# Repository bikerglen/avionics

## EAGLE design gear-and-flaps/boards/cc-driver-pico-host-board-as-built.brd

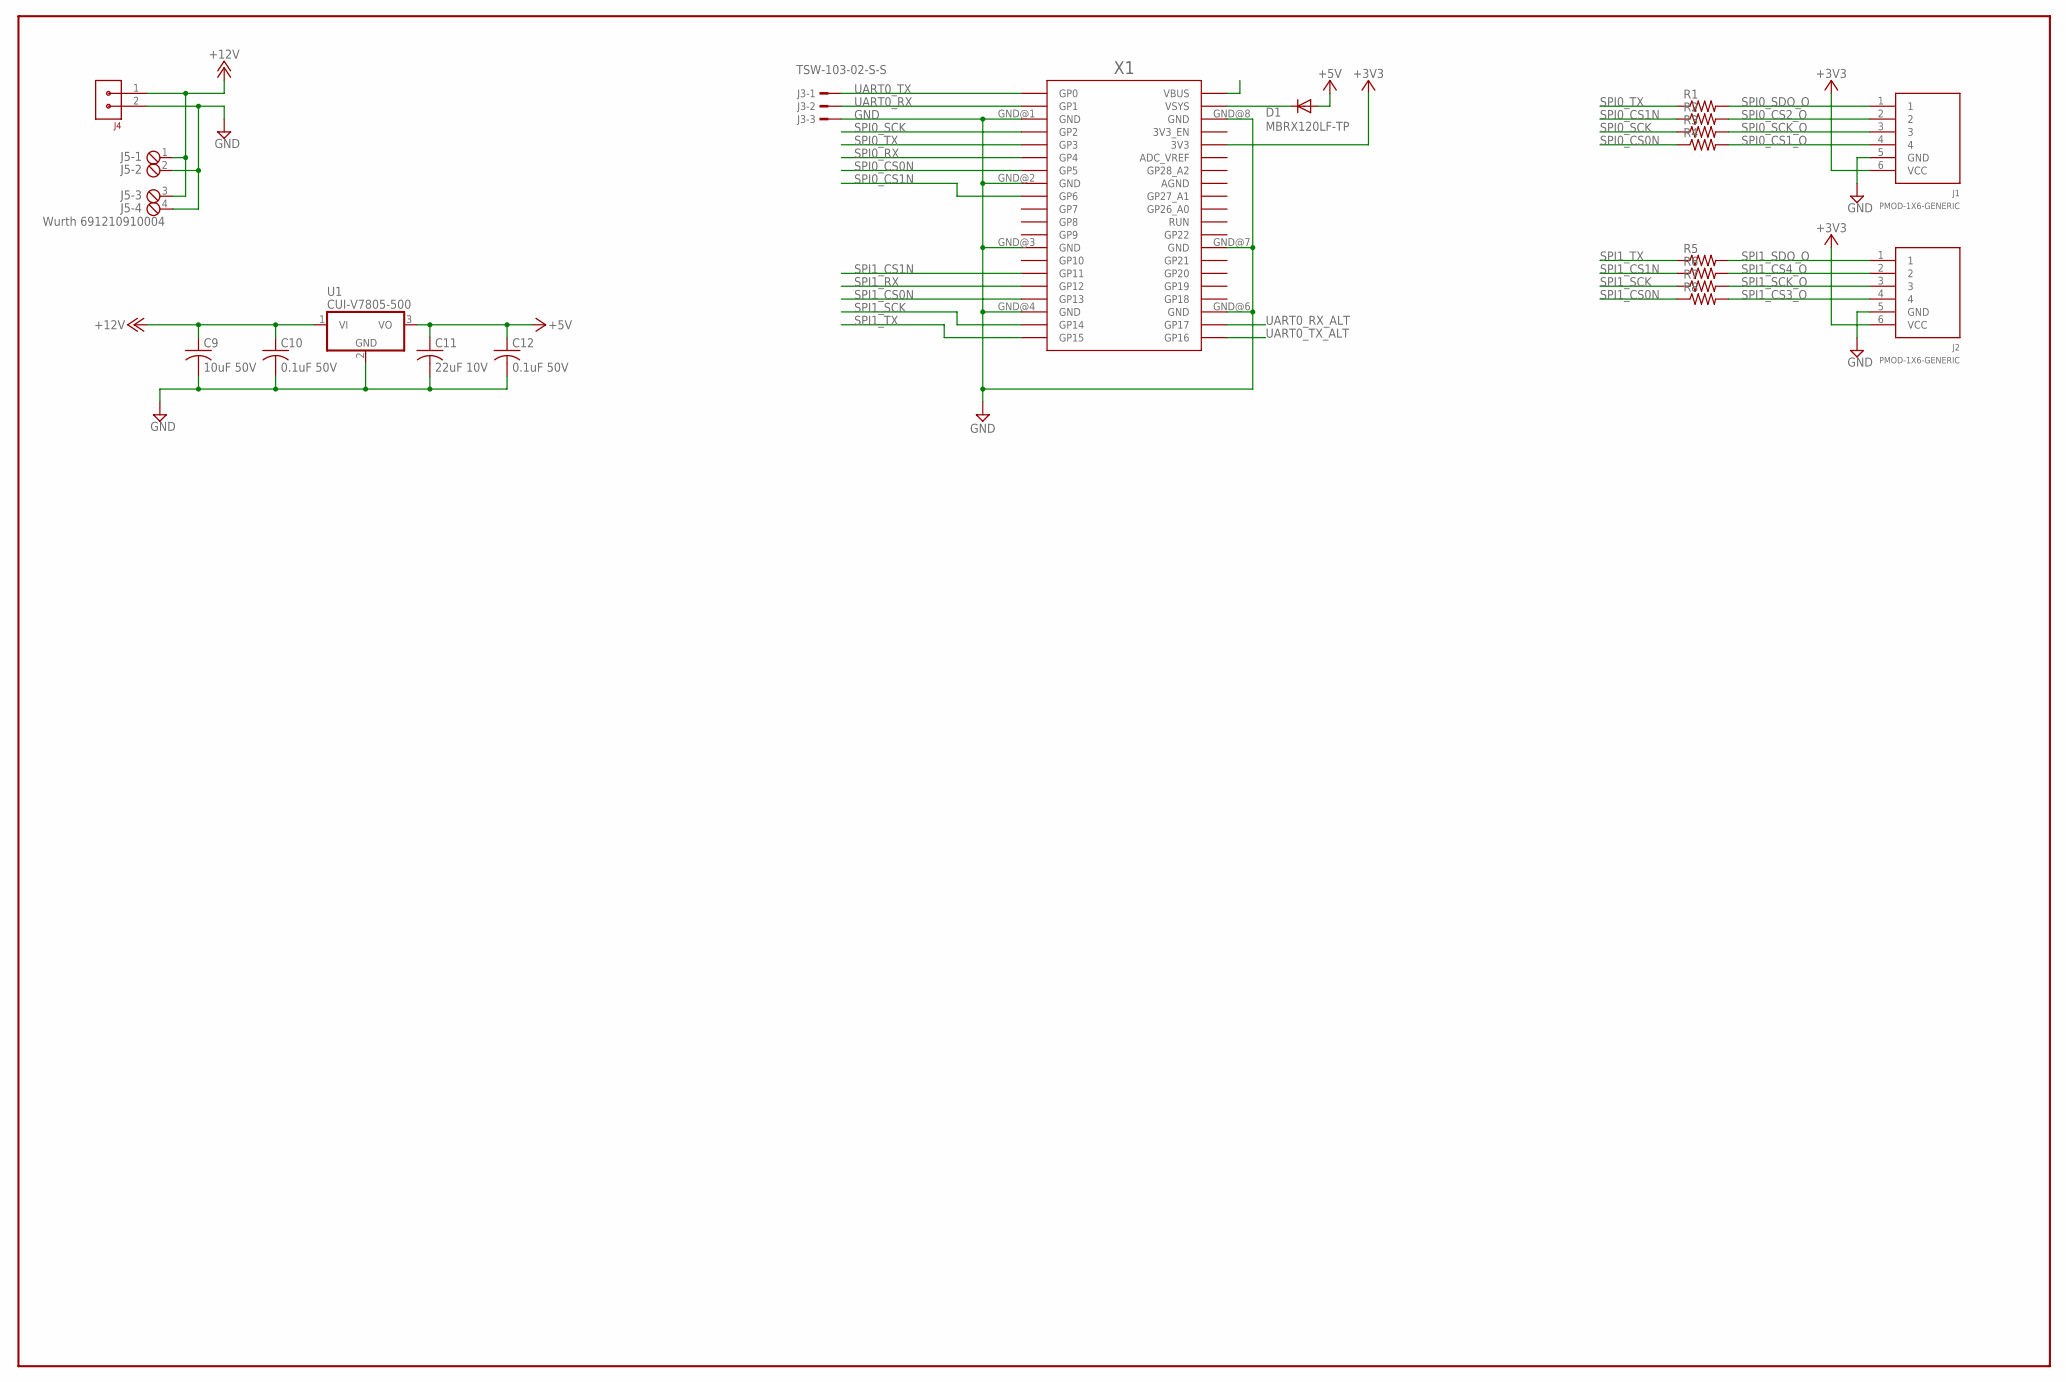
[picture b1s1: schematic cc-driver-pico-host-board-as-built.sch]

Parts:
C9: 10uF 50V; C1210K; MFR_PART_NO C1210C106K5RACTU
C10, C12: 0.1uF 50V; C1206K; MFR_PART_NO C1206S104M5RACTU
C11: 22uF 10V; C1206K; MFR_PART_NO C1206C226K8RAC7800
D1: MBRX120LF-TP; SOD123
J1, J2: PMOD-1X6-GENERIC; CON-PMOD-1X6
J3: TSW-103-02-S-S
J4: CON-3.81MM-1X2-PHOENIX; CON-PHOENIX-3.81-1X2-RA
J5: Wurth 691210910004; 4POL254
R1, R2, R3, R4, R5, R6, R7, R8: R-US_R0603; R0603
U1: CUI-V7805-500; CUI-78XX-500
X1: RPI_PICO_IG-TH; RPI_PICO_TH

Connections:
+3V3: J1.6 (VCC), J2.6 (VCC), X1.3V3
+5V: C11.1, C12.1, D1.A, U1.3 (VO)
+12V: C9.1, C10.1, J4.1, J5.1, J5.3, U1.1 (VI)
GND: C9.2, C10.2, C11.2, C12.2, J1.5 (GND), J2.5 (GND), J3.3, J4.2, J5.2, J5.4, U1.2 (GND), X1.GND@1 (GND), X1.GND@2 (GND), X1.GND@3 (GND), X1.GND@4 (GND), X1.GND@6 (GND), X1.GND@7 (GND), X1.GND@8 (GND)
SPI0_CS0N: R4.1, X1.GP5
SPI0_CS1N: R2.1, X1.GP6
SPI0_CS1_O: J1.4, R4.2
SPI0_CS2_O: J1.2, R2.2
SPI0_RX: X1.GP4
SPI0_SCK: R3.1, X1.GP2
SPI0_SCK_O: J1.3, R3.2
SPI0_SDO_O: J1.1, R1.2
SPI0_TX: R1.1, X1.GP3
SPI1_CS0N: R8.1, X1.GP13
SPI1_CS1N: R6.1, X1.GP11
SPI1_CS3_O: J2.4, R8.2
SPI1_CS4_O: J2.2, R6.2
SPI1_RX: X1.GP12
SPI1_SCK: R7.1, X1.GP14
SPI1_SCK_O: J2.3, R7.2
SPI1_SDO_O: J2.1, R5.2
SPI1_TX: R5.1, X1.GP15
UART0_RX: J3.2, X1.GP1
UART0_RX_ALT: X1.GP17
UART0_TX: J3.1, X1.GP0
UART0_TX_ALT: X1.GP16
VSYS: D1.C, X1.VSYS

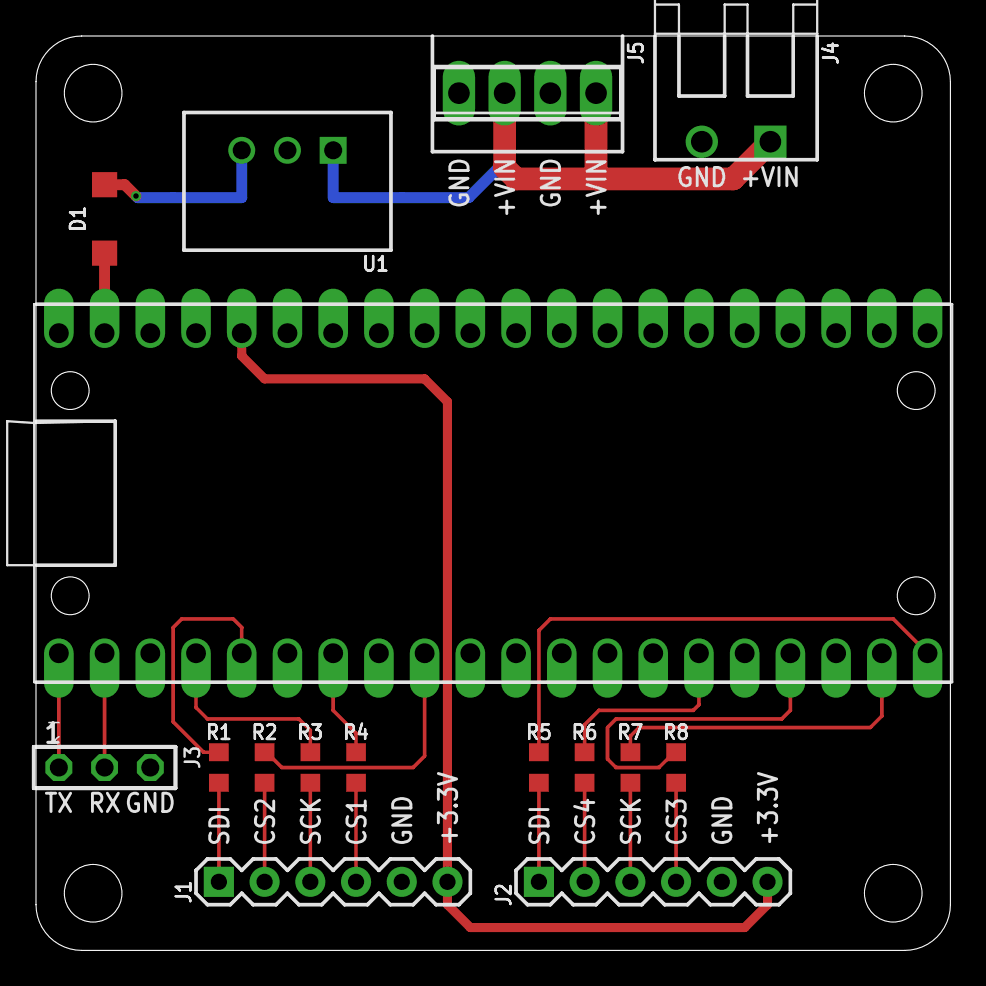
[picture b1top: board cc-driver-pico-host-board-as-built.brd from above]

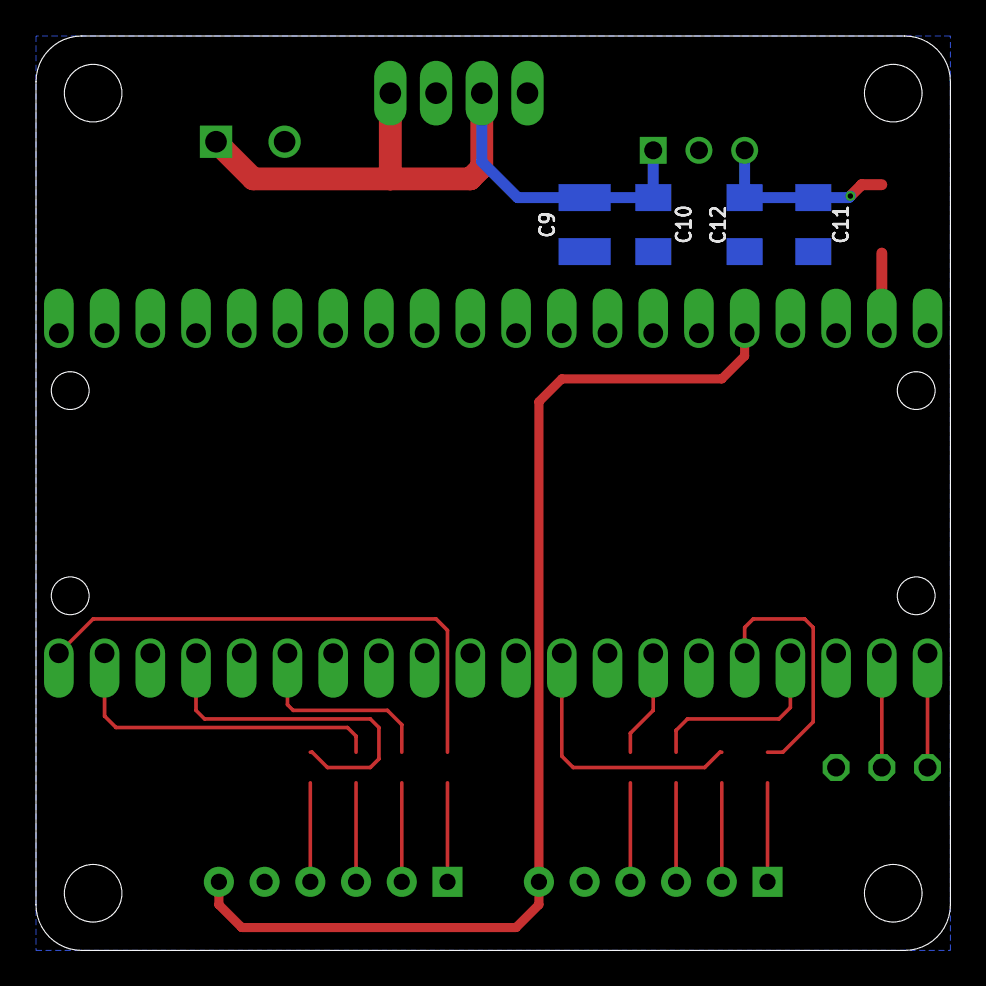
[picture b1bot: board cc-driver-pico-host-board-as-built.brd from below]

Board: 2 copper layers, 50.8 x 50.8 mm, 20 parts (4 on the bottom side), 23 nets.

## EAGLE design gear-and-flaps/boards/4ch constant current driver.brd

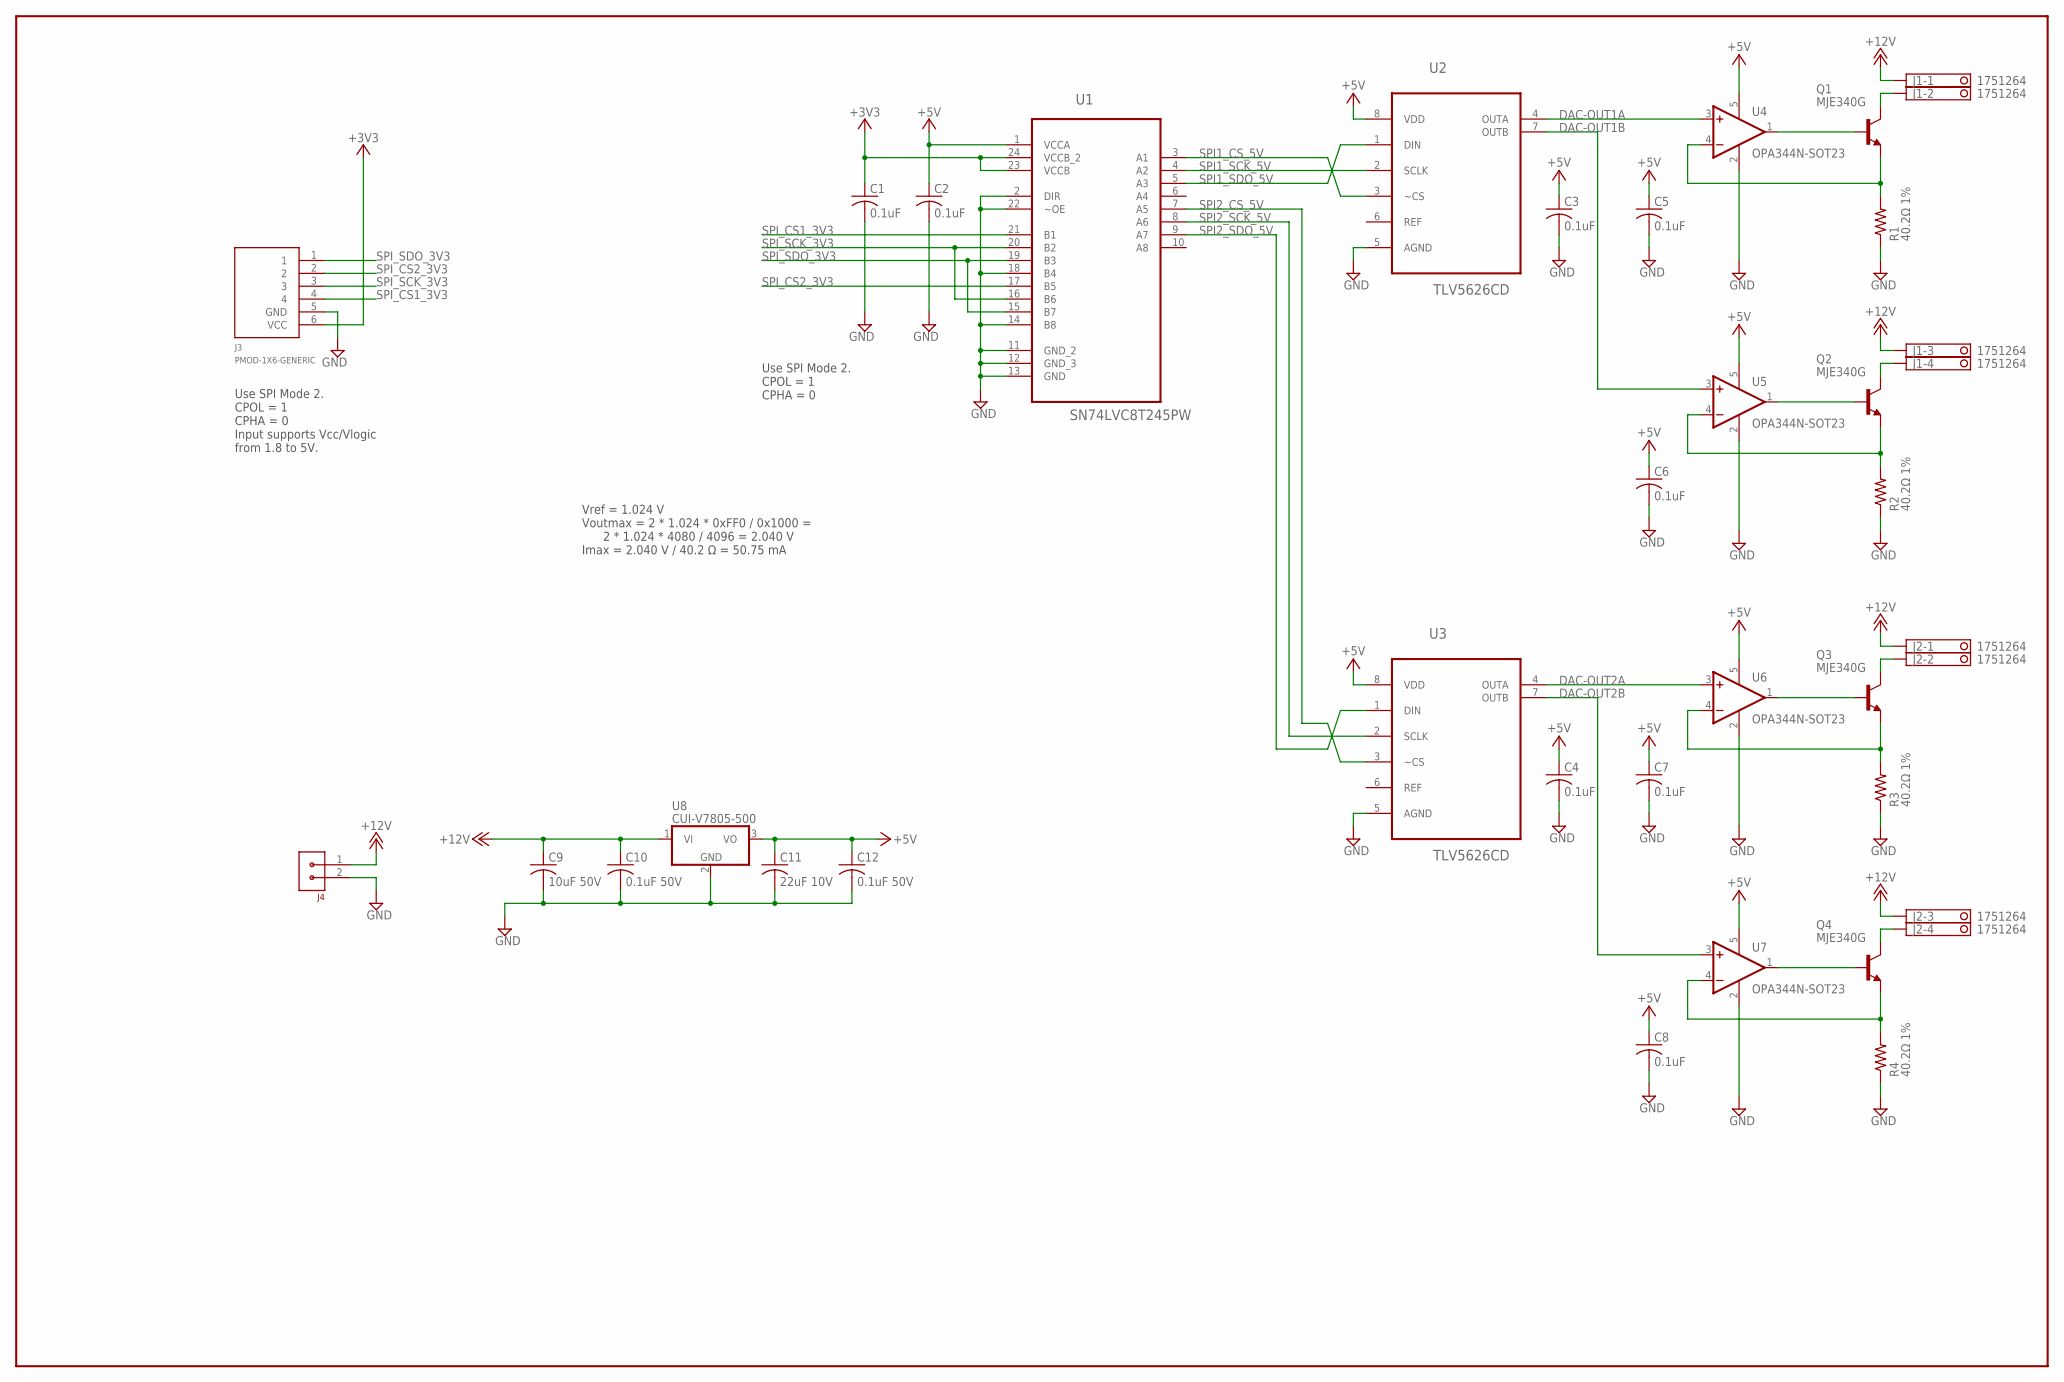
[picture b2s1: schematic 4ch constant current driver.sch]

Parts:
C1, C2, C3, C4, C5, C6, C7, C8: 0.1uF; C0603K; MFR_PART_NO C1206C104K5RACAUTO
C9: 10uF 50V; C1210K; MFR_PART_NO C1210C106K5RACTU
C10, C12: 0.1uF 50V; C1206K; MFR_PART_NO C1206S104M5RACTU
C11: 22uF 10V; C1206K; MFR_PART_NO C1206C226K8RAC7800
J1, J2: 1751264
J3: PMOD-1X6-GENERIC; CON-PMOD-1X6
J4: CON-3.81MM-1X2-PHOENIX; CON-PHOENIX-3.81-1X2-RA
Q1, Q2, Q3, Q4: MJE340G; TO126V; MFR_PART_NO MJE340G
R1, R2, R3, R4: 40.2Ω 1%; R1210; MFR_PART_NO ERJ-14NF73R2U
U1: SN74LVC8T245PW; SOP65P640X120-24N; MFR_PART_NO SN74LVC8T245PW
U2, U3: TLV5626CD; SOIC127P600X175-8N; MFR_PART_NO TLV5626CD
U4, U5, U6, U7: OPA344N-SOT23; SOT23-5; MFR_PART_NO OPA344NA/3K
U8: CUI-V7805-500; CUI-78XX-500

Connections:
+3V3: C1.1, J3.6 (VCC), U1.23 (VCCB), U1.24 (VCCB_2)
+5V: C2.1, C3.1, C4.1, C5.1, C6.1, C7.1, C8.1, C11.1, C12.1, U1.1 (VCCA), U2.8 (VDD), U3.8 (VDD), U4.5 (V+), U5.5 (V+), U6.5 (V+), U7.5 (V+), U8.3 (VO)
+12V: C9.1, C10.1, J1.1, J1.3, J2.1, J2.3, J4.1, U8.1 (VI)
DAC-OUT1A: U2.4 (OUTA), U4.3 (+IN)
DAC-OUT1B: U2.7 (OUTB), U5.3 (+IN)
DAC-OUT2A: U3.4 (OUTA), U6.3 (+IN)
DAC-OUT2B: U3.7 (OUTB), U7.3 (+IN)
GND: C1.2, C2.2, C3.2, C4.2, C5.2, C6.2, C7.2, C8.2, C9.2, C10.2, C11.2, C12.2, J3.5 (GND), J4.2, R1.1, R2.1, R3.1, R4.1, U1.2 (DIR), U1.11 (GND_2), U1.12 (GND_3), U1.13 (GND), U1.14 (B8), U1.18 (B4), U1.22 (~OE), U2.5 (AGND), U3.5 (AGND), U4.2 (V-), U5.2 (V-), U6.2 (V-), U7.2 (V-), U8.2 (GND)
unnamed: Q1.1 (E), R1.2, U4.4 (-IN)
unnamed: Q3.1 (E), R3.2, U6.4 (-IN)
unnamed: Q1.3 (B), U4.1 (OUT)
unnamed: Q3.3 (B), U6.1 (OUT)
unnamed: Q4.1 (E), R4.2, U7.4 (-IN)
unnamed: Q4.3 (B), U7.1 (OUT)
unnamed: Q2.1 (E), R2.2, U5.4 (-IN)
unnamed: Q2.3 (B), U5.1 (OUT)
OUT1A: J1.2, Q1.2 (C)
OUT1B: J1.4, Q2.2 (C)
OUT2A: J2.2, Q3.2 (C)
OUT2B: J2.4, Q4.2 (C)
SPI1_CS_5V: U1.3 (A1), U2.3 (~CS)
SPI1_SCK_5V: U1.4 (A2), U2.2 (SCLK)
SPI1_SDO_5V: U1.5 (A3), U2.1 (DIN)
SPI2_CS_5V: U1.7 (A5), U3.3 (~CS)
SPI2_SCK_5V: U1.8 (A6), U3.2 (SCLK)
SPI2_SDO_5V: U1.9 (A7), U3.1 (DIN)
SPI_CS1_3V3: J3.4, U1.21 (B1)
SPI_CS2_3V3: J3.2, U1.17 (B5)
SPI_SCK_3V3: J3.3, U1.16 (B6), U1.20 (B2)
SPI_SDO_3V3: J3.1, U1.15 (B7), U1.19 (B3)

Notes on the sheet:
Use SPI Mode 2. CPOL = 1 CPHA = 0
Use SPI Mode 2. CPOL = 1 CPHA = 0 Input supports Vcc/Vlogic from 1.8 to 5V.
Vref = 1.024 V Voutmax = 2 * 1.024 * 0xFF0 / 0x1000 = 2 * 1.024 * 4080 / 4096 = 2.040 V Imax = 2.040 V / 40.2 Ω = 50.75 mA

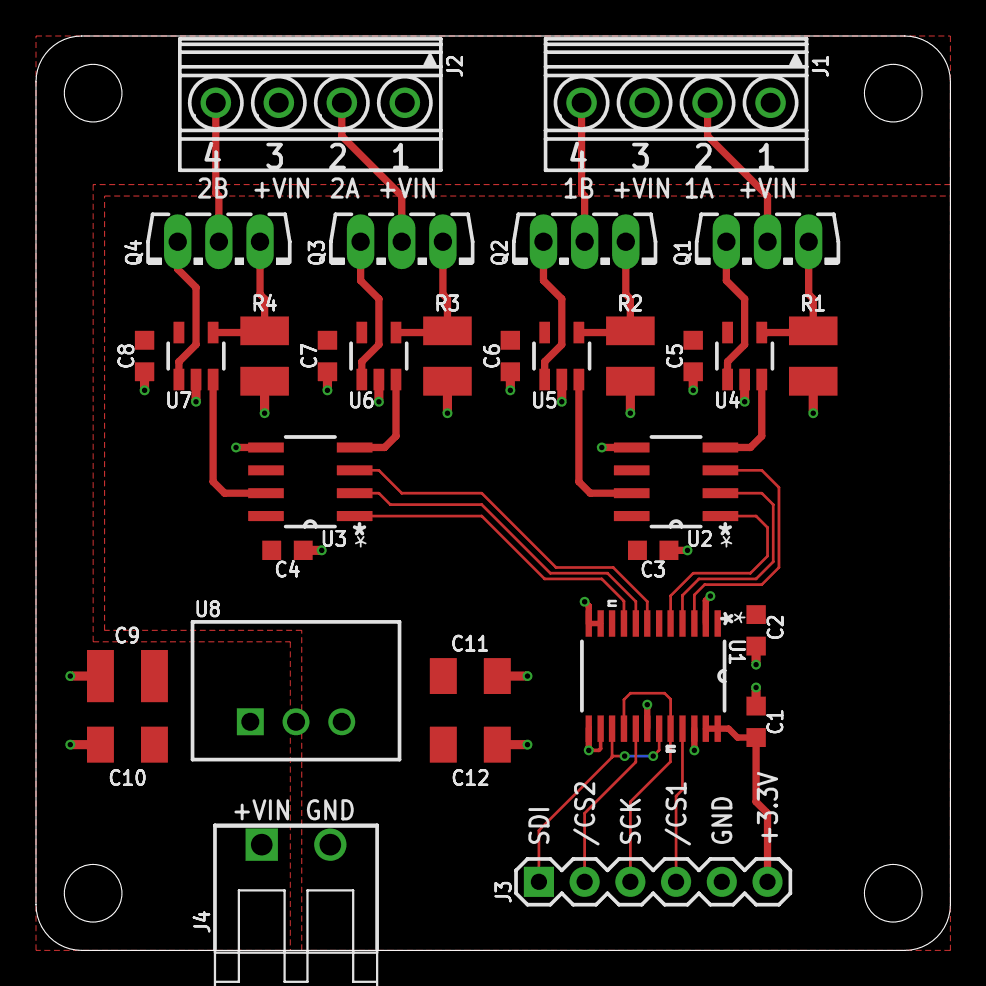
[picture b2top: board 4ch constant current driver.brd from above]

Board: 2 copper layers, 50.8 x 50.8 mm, 32 parts (0 on the bottom side), 30 nets.

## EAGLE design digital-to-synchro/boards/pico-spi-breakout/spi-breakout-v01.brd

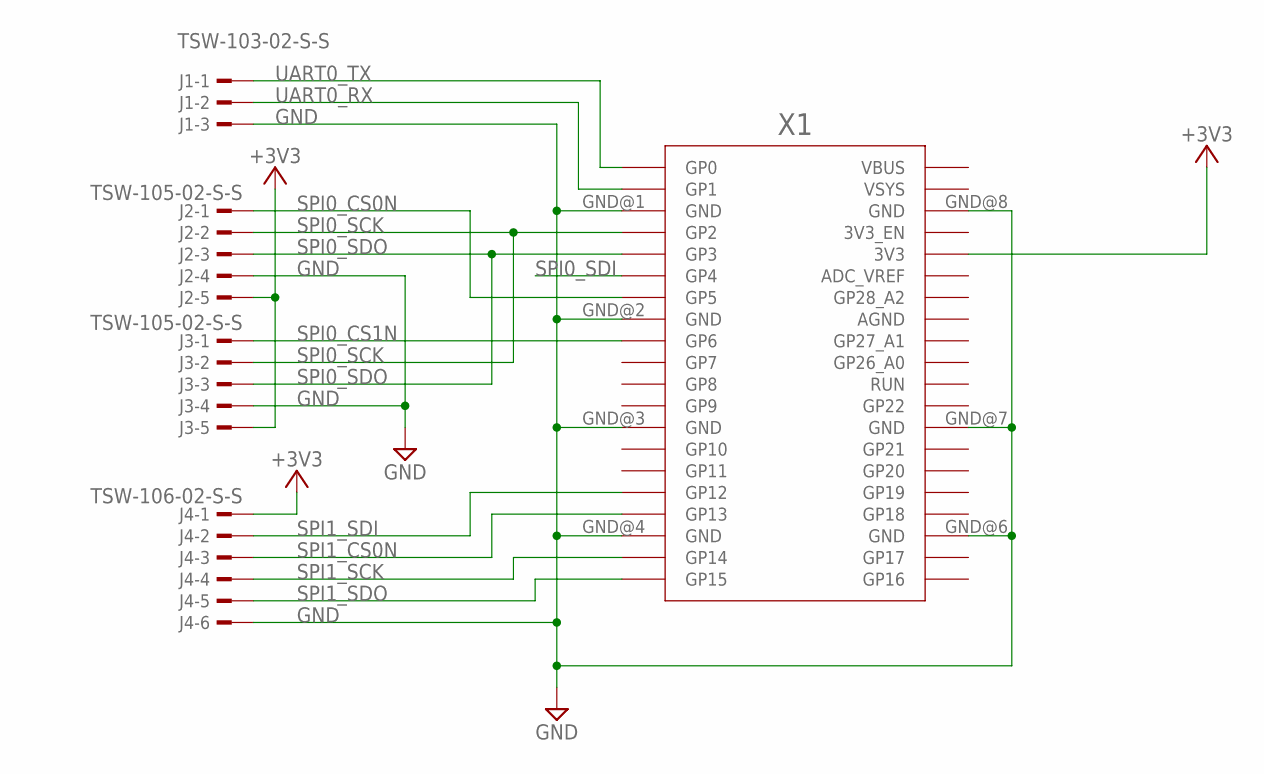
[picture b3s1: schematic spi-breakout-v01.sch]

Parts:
J1: TSW-103-02-S-S
J2, J3: TSW-105-02-S-S
J4: TSW-106-02-S-S
X1: RPI_PICO_IG-TH; RPI_PICO_TH

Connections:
+3V3: J2.5, J3.5, J4.1, X1.3V3
GND: J1.3, J2.4, J3.4, J4.6, X1.GND@1 (GND), X1.GND@2 (GND), X1.GND@3 (GND), X1.GND@4 (GND), X1.GND@6 (GND), X1.GND@7 (GND), X1.GND@8 (GND)
SPI0_CS0N: J2.1, X1.GP5
SPI0_CS1N: J3.1, X1.GP6
SPI0_SCK: J2.2, J3.2, X1.GP2
SPI0_SDI: X1.GP4
SPI0_SDO: J2.3, J3.3, X1.GP3
SPI1_CS0N: J4.3, X1.GP13
SPI1_SCK: J4.4, X1.GP14
SPI1_SDI: J4.2, X1.GP12
SPI1_SDO: J4.5, X1.GP15
UART0_RX: J1.2, X1.GP1
UART0_TX: J1.1, X1.GP0

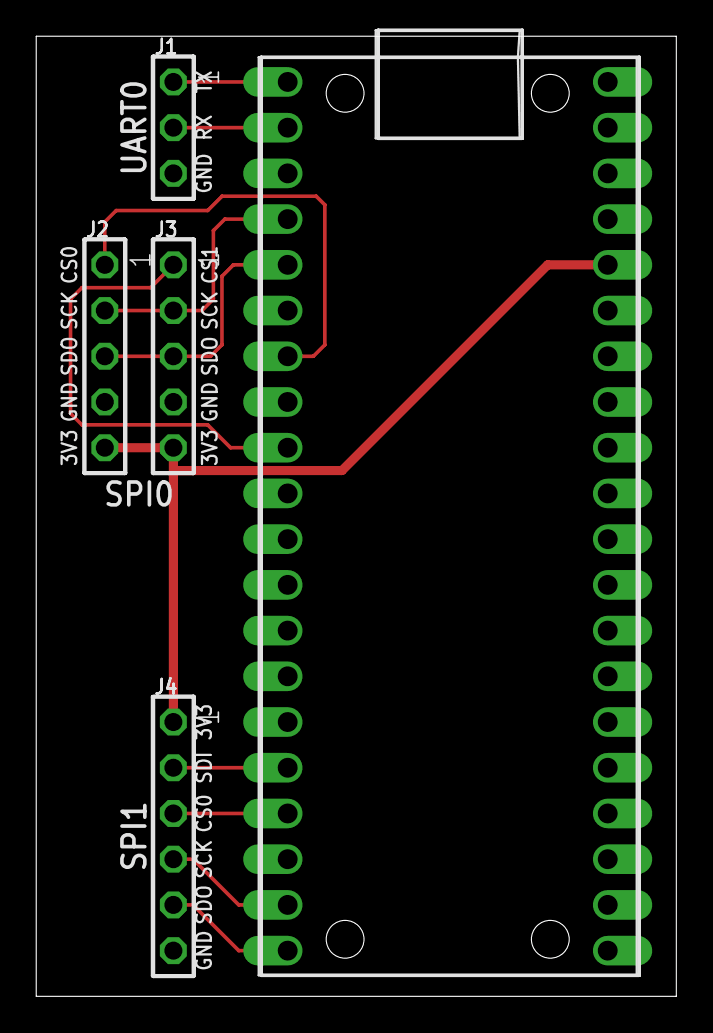
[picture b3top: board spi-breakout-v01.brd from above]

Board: 2 copper layers, 35.6 x 53.3 mm, 5 parts (0 on the bottom side), 12 nets.

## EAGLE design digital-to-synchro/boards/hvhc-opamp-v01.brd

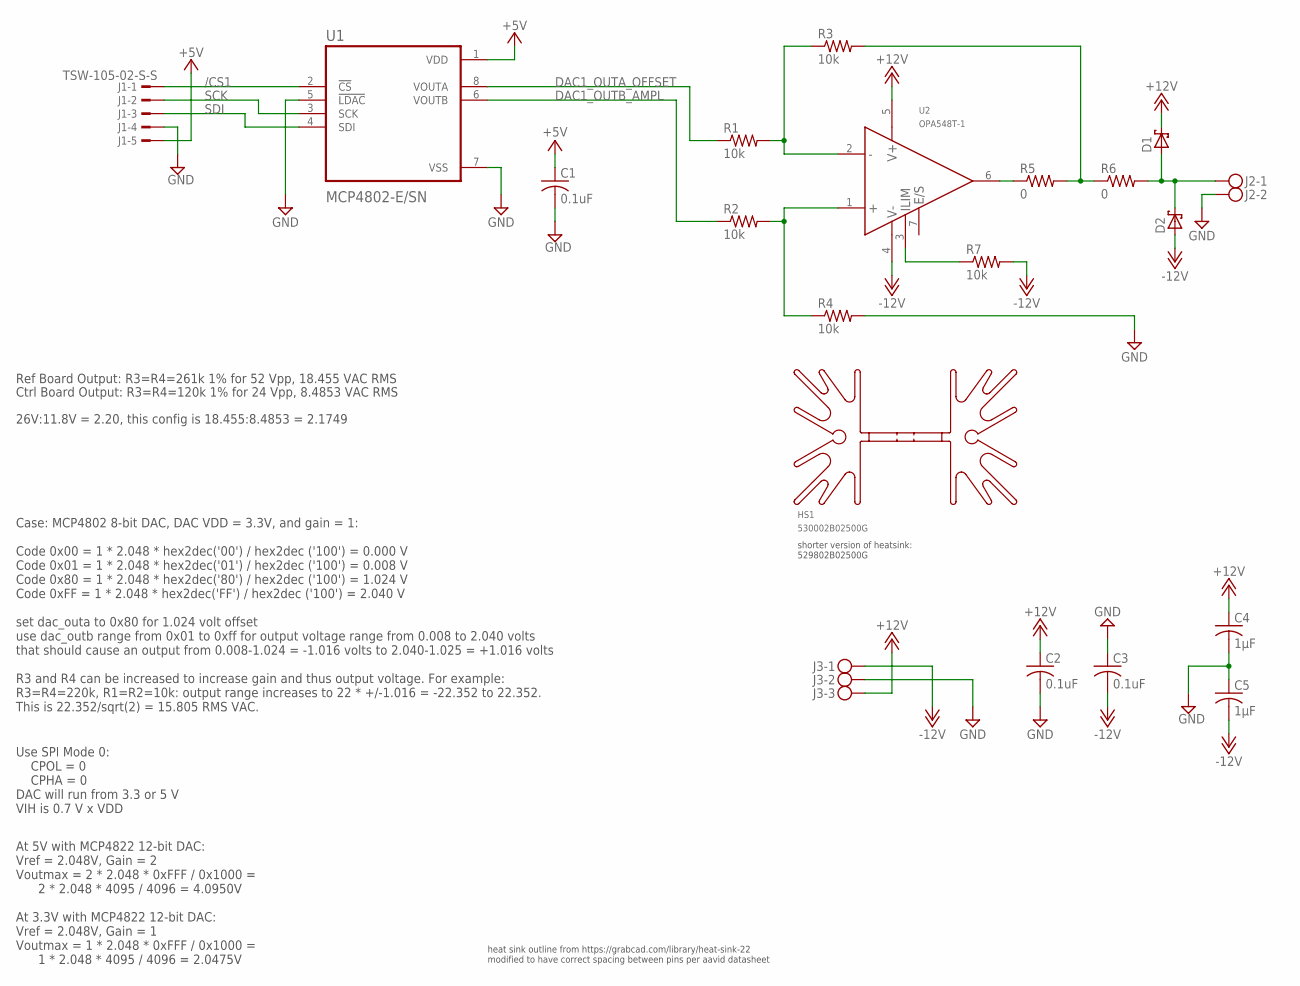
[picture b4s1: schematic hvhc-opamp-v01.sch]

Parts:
C1, C2, C3: 0.1uF; C0603K; MFR_PART_NO C1206C104K5RACAUTO
C4, C5: 1µF; C1206K
D1, D2: 1N5819-B; DO41-7.6
HS1: 530002B02500G
J1: TSW-105-02-S-S
J2: 1711725
J3: 1711738
R1, R2, R3, R4, R7: 10k; R1206
R5, R6: 0; R1206
U1: MCP4802-E/SN; SOIC127P600X175-8N
U2: OPA548T-1; TO220-7-KC

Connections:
+: R2.2, R4.1, U2.1 (VIN+)
+5V: C1.1, J1.5, U1.1 (VDD)
+12V: C2.1, C4.1, D1.C, J3.3, U2.5 (V+)
-: R1.2, R3.1, U2.2 (VIN-)
-12V: C3.2, C5.2, D2.A, J3.1, R7.2, U2.4 (V-)
/CS1: J1.1, U1.2 (!CS)
DAC1_OUTA_OFFSET: R1.1, U1.8 (VOUTA)
DAC1_OUTB_AMPL: R2.1, U1.6 (VOUTB)
GND: C1.2, C2.2, C3.1, C4.2, C5.1, J1.4, J2.2, J3.2, R4.2, U1.5 (!LDAC), U1.7 (VSS)
unnamed: R5.1, U2.6 (VO)
unnamed: D1.A, D2.C, J2.1, R6.2
unnamed: R7.1, U2.3 (ILIM)
OUT: R3.2, R5.2, R6.1
SCK: J1.2, U1.3 (SCK)
SDI: J1.3, U1.4 (SDI)

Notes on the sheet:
At 5V with MCP4822 12-bit DAC: Vref = 2.048V, Gain = 2 Voutmax = 2 * 2.048 * 0xFFF / 0x1000 = 2 * 2.048 * 4095 / 4096 = 4.0950V At 3.3V with MCP4822 12-bit DAC: Vref = 2.048V, Gain = 1 Voutmax = 1 * 2.048 * 0xFFF / 0x1000 = 1 * 2.048 * 4095 / 4096 = 2.0475V
Use SPI Mode 0: CPOL = 0 CPHA = 0 DAC will run from 3.3 or 5 V VIH is 0.7 V x VDD
Case: MCP4802 8-bit DAC, DAC VDD = 3.3V, and gain = 1: Code 0x00 = 1 * 2.048 * hex2dec('00') / hex2dec ('100') = 0.000 V Code 0x01 = 1 * 2.048 * hex2dec('01') / hex2dec ('100') = 0.008 V Code 0x80 = 1 * 2.048 * hex2dec('80') / hex2dec ('100') = 1.024 V Code 0xFF = 1 * 2.048 * hex2dec('FF') / hex2de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
shorter version of heatsink: 529802B02500G
heat sink outline from https://grabcad.com/library/heat-sink-22 modified to have correct spacing between pins per aavid datasheet
Ref Board Output: R3=R4=261k 1% for 52 Vpp, 18.455 VAC RMS
Ctrl Board Output: R3=R4=120k 1% for 24 Vpp, 8.4853 VAC RMS
26V:11.8V = 2.20, this config is 18.455:8.4853 = 2.1749

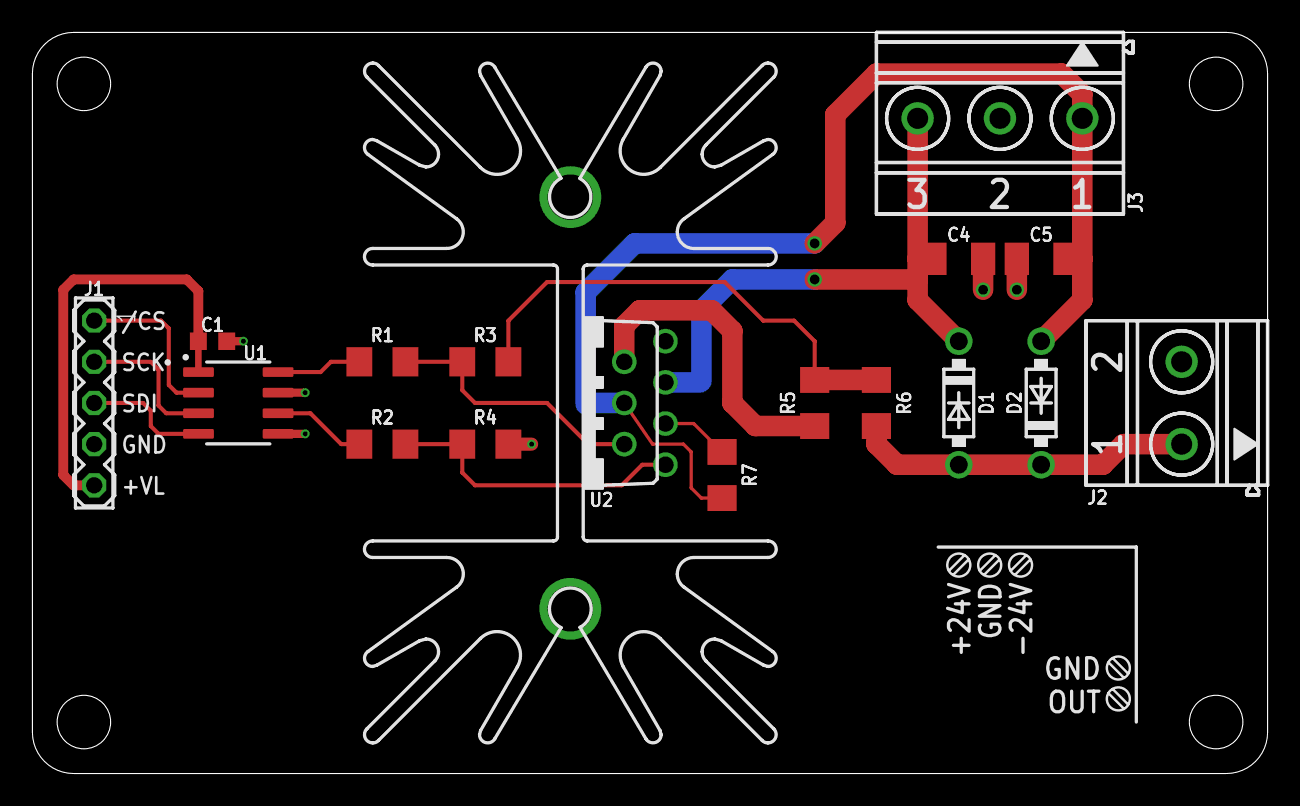
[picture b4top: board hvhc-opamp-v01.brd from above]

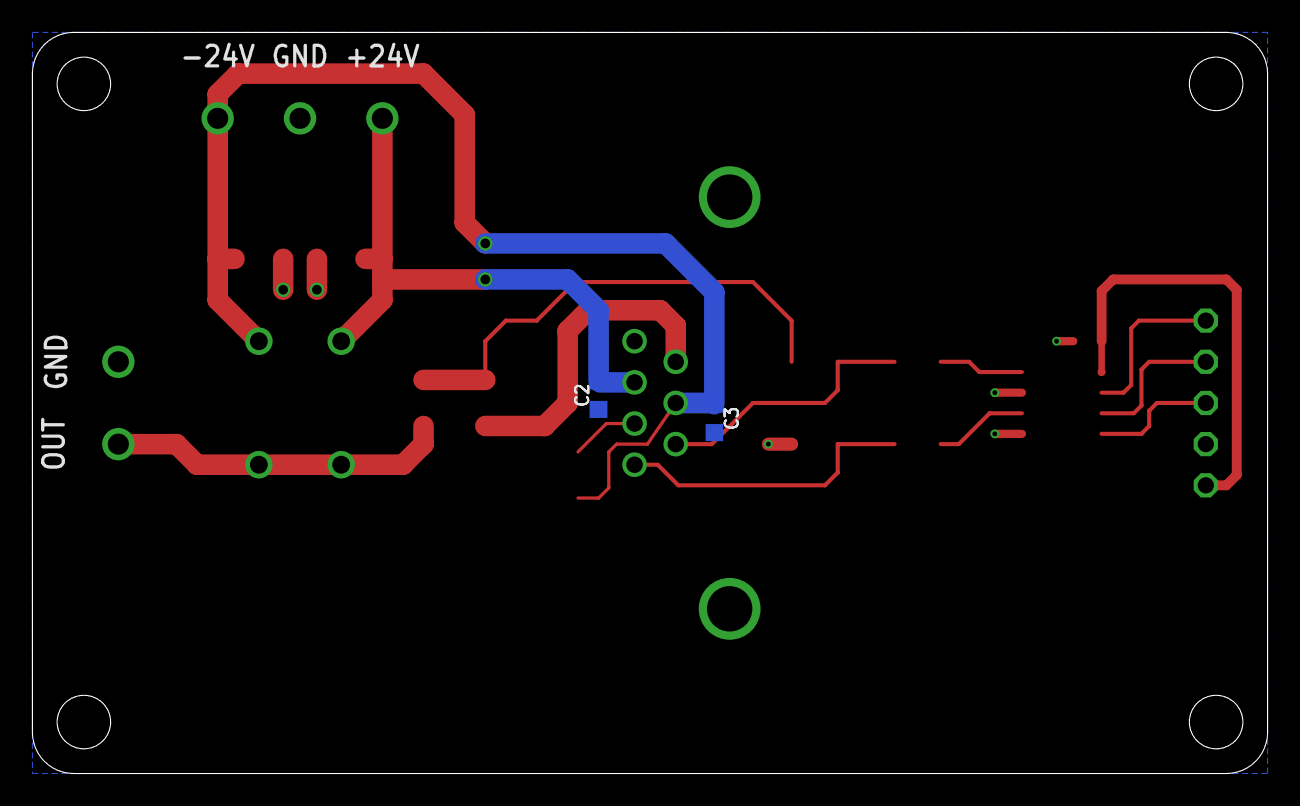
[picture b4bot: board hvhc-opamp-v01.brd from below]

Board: 2 copper layers, 76.2 x 45.7 mm, 20 parts (2 on the bottom side), 15 nets.

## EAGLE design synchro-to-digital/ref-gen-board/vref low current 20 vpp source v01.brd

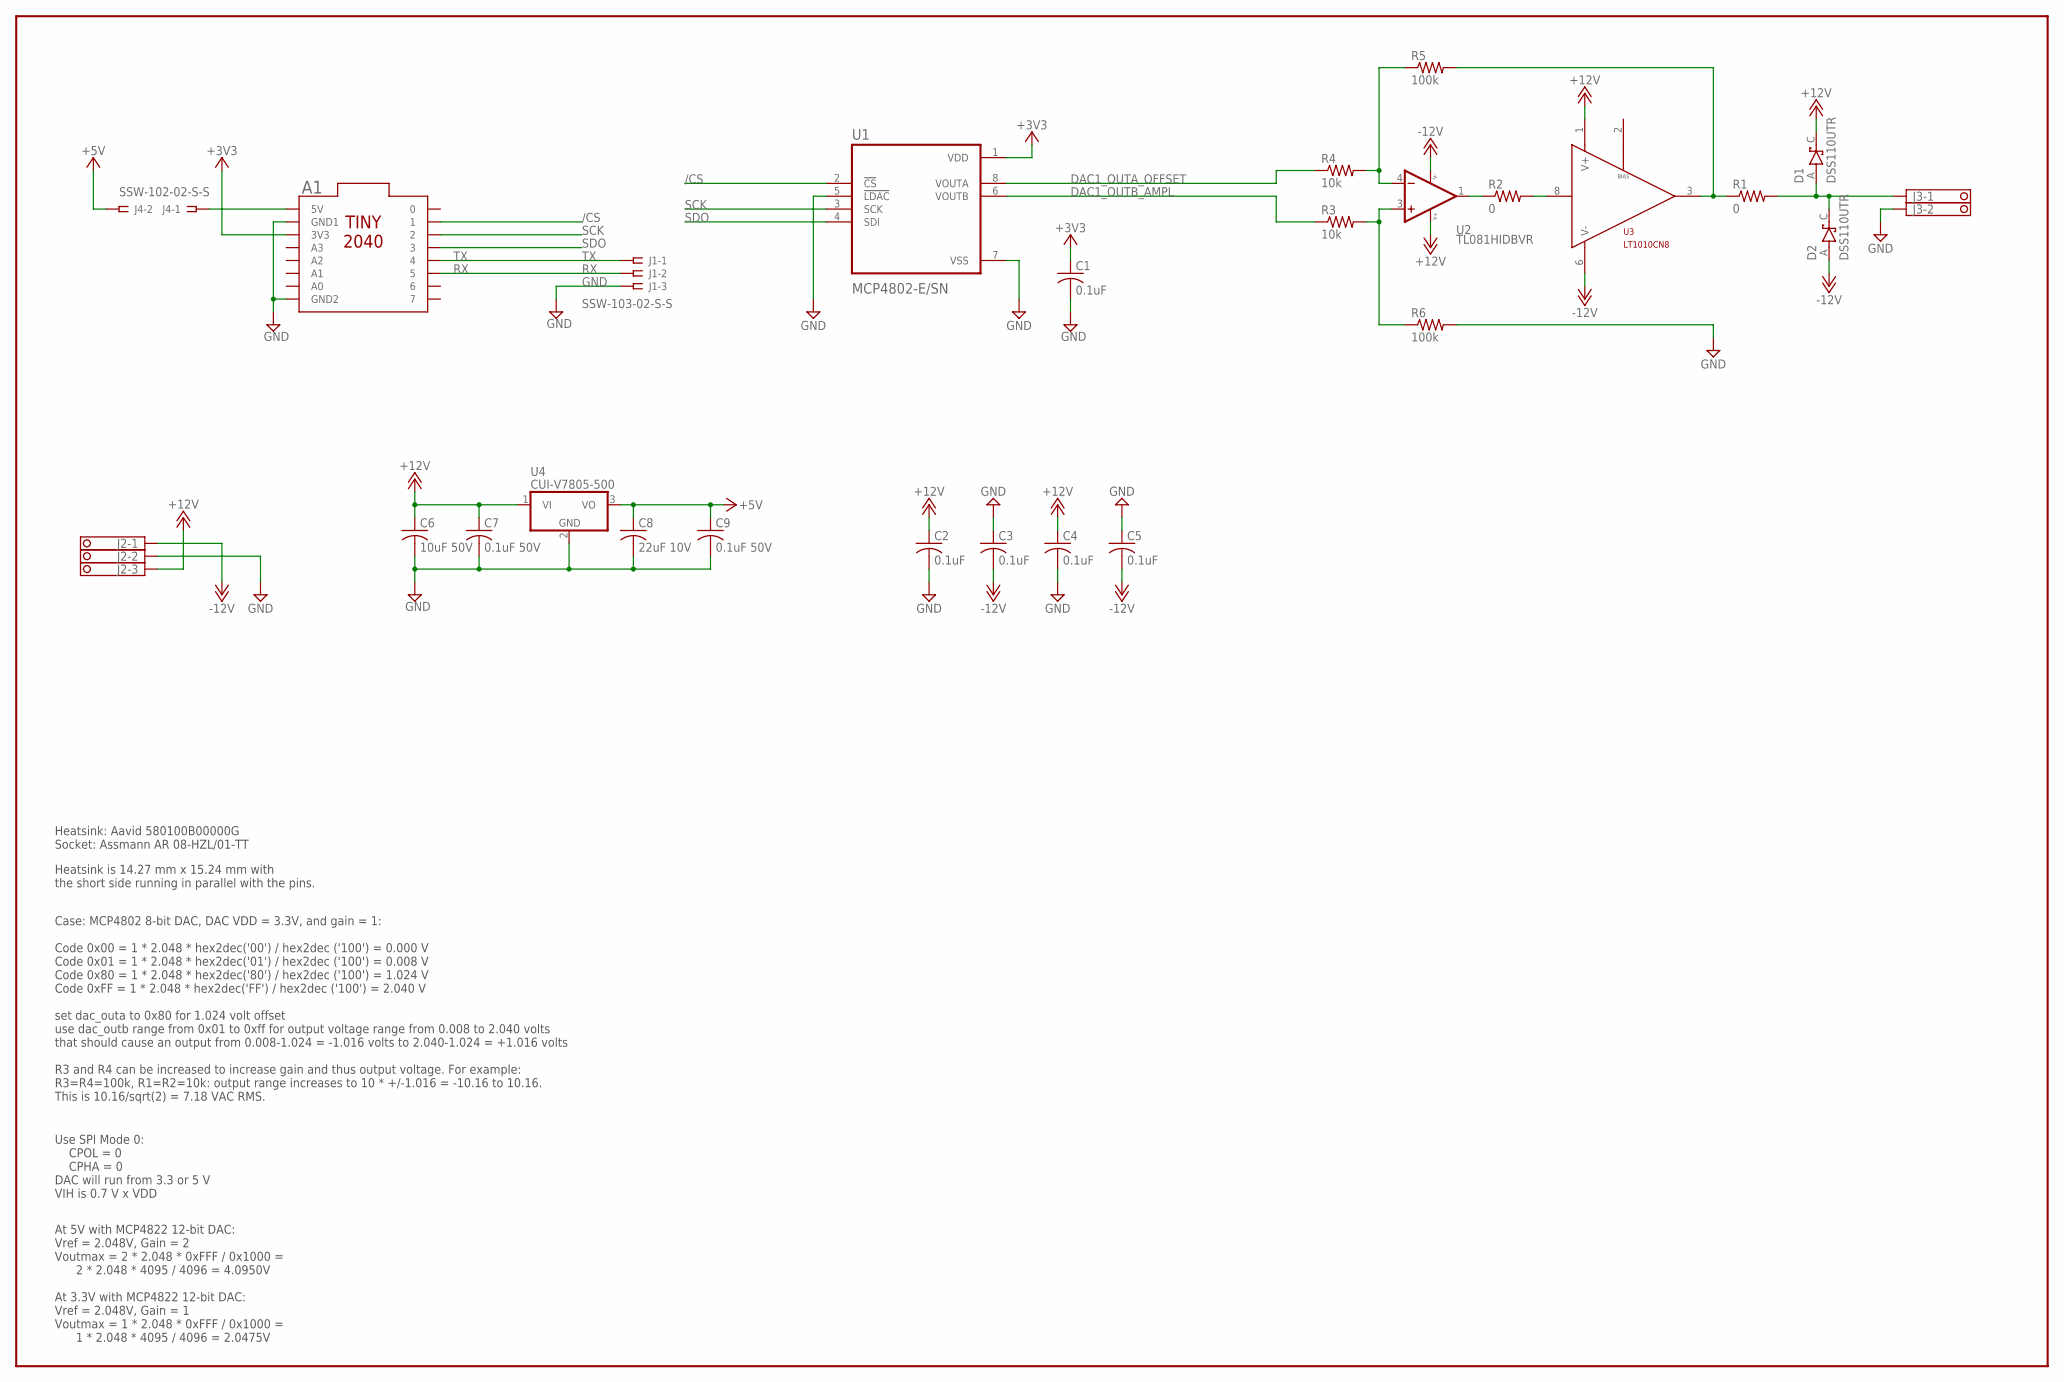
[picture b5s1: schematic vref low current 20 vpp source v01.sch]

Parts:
A1: TINY2040PTHLOCK; TINY2040_PTH_LOCK
C1, C2, C3, C4, C5: 0.1uF; C0603K; MFR_PART_NO C1206C104K5RACAUTO
C6: 10uF 50V; C1210K; MFR_PART_NO C1210C106K5RACTU
C7, C9: 0.1uF 50V; C1206K; MFR_PART_NO C1206S104M5RACTU
C8: 22uF 10V; C1206K; MFR_PART_NO C1206C226K8RAC7800
D1, D2: DSS110UTR; SODFL3618X110N
J1: SSW-103-02-S-S
J2: 1751251
J3: 1751248
J4: SSW-102-02-S-S
R1, R2: 0; R1206
R3, R4: 10k; R1206
R5, R6: 100k; R1206
U1: MCP4802-E/SN; SOIC127P600X175-8N
U2: TL081HIDBVR; SOT-23-5_DBV_TEX
U3: LT1010CN8; DIL08
U4: CUI-V7805-500; CUI-78XX-500

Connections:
+: R3.2, R6.1, U2.3 (IN+)
+3V3: A1.3V3, C1.1, U1.1 (VDD)
+5V: C8.1, C9.1, J4.2, U4.3 (VO)
+12V: C2.1, C4.1, C6.1, C7.1, D1.C (K), J2.3, U2.5 (V+), U3.1 (V+), U4.1 (VI)
-: R4.2, R5.1, U2.4 (IN-)
-12V: C3.2, C5.2, D2.A, J2.1, U2.2 (V-), U3.6 (V-)
/CS: A1.1, U1.2 (!CS)
DAC1_OUTA_OFFSET: R4.1, U1.8 (VOUTA)
DAC1_OUTB_AMPL: R3.1, U1.6 (VOUTB)
GND: A1.GND1, A1.GND2, C1.2, C2.2, C3.1, C4.2, C5.1, C6.2, C7.2, C8.2, C9.2, J1.3, J2.2, J3.2, R6.2, U1.5 (!LDAC), U1.7 (VSS), U4.2 (GND)
unnamed: R2.1, U2.1 (OUT)
unnamed: D1.A, D2.C (K), J3.1, R1.2
unnamed: A1.5V, J4.1
unnamed: R2.2, U3.8 (INPUT)
OUT: R1.1, R5.2, U3.3 (OUTPUT)
RX: A1.5, J1.2
SCK: A1.2, U1.3 (SCK)
SDO: A1.3, U1.4 (SDI)
TX: A1.4, J1.1

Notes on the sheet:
Heatsink: Aavid 580100B00000G Socket: Assmann AR 08-HZL/01-TT
Heatsink is 14.27 mm x 15.24 mm with the short side running in parallel with the pins.
At 5V with MCP4822 12-bit DAC: Vref = 2.048V, Gain = 2 Voutmax = 2 * 2.048 * 0xFFF / 0x1000 = 2 * 2.048 * 4095 / 4096 = 4.0950V At 3.3V with MCP4822 12-bit DAC: Vref = 2.048V, Gain = 1 Voutmax = 1 * 2.048 * 0xFFF / 0x1000 = 1 * 2.048 * 4095 / 4096 = 2.0475V
Use SPI Mode 0: CPOL = 0 CPHA = 0 DAC will run from 3.3 or 5 V VIH is 0.7 V x VDD
Case: MCP4802 8-bit DAC, DAC VDD = 3.3V, and gain = 1: Code 0x00 = 1 * 2.048 * hex2dec('00') / hex2dec ('100') = 0.000 V Code 0x01 = 1 * 2.048 * hex2dec('01') / hex2dec ('100') = 0.008 V Code 0x80 = 1 * 2.048 * hex2dec('80') / hex2dec ('100') = 1.024 V Code 0xFF = 1 * 2.048 * hex2dec('FF') / hex2de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

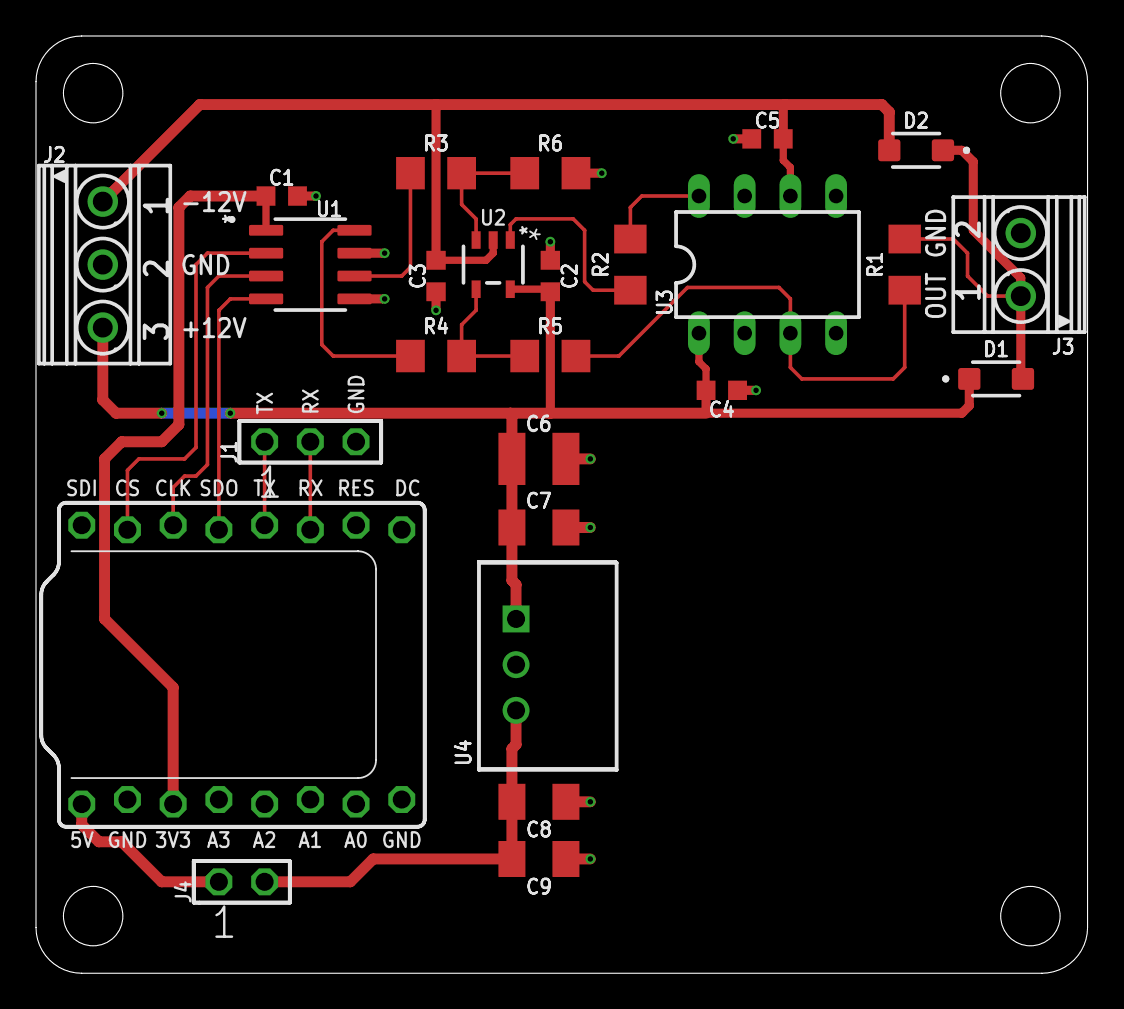
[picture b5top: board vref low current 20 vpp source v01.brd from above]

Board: 2 copper layers, 58.4 x 52.1 mm, 26 parts (0 on the bottom side), 19 nets.

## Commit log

2023-01-18 initial checkin
2023-01-20 add ltspice sim model of opamp in ref volt source
2023-01-22 add RP2040 dual core 400 Hz CW generator code
2023-01-22 add board schematic and layout
2023-01-22 rename board files
2023-01-23 fix led for tiny2040 board
2023-02-11 check in digital to synchro rpi pico code
2023-02-17 initial checkin; pid loop works well; rest of code subject to change
2023-02-17 add eagle files and png images of eagle files
2023-02-17 move board files to power arb directory
2023-02-17 add pico spi breakout board
2023-02-17 rename directory
2023-02-17 move pico software to software directory
2023-02-17 center parts on schematic
2023-02-21 Create LICENSE
2024-11-13 add constant current boards and software for ge landing gear and flaps indicator

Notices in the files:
parts and their libraries:
COPYRIGHT: Copyright (C) 2022 Ultra Librarian. All rights reserved.
